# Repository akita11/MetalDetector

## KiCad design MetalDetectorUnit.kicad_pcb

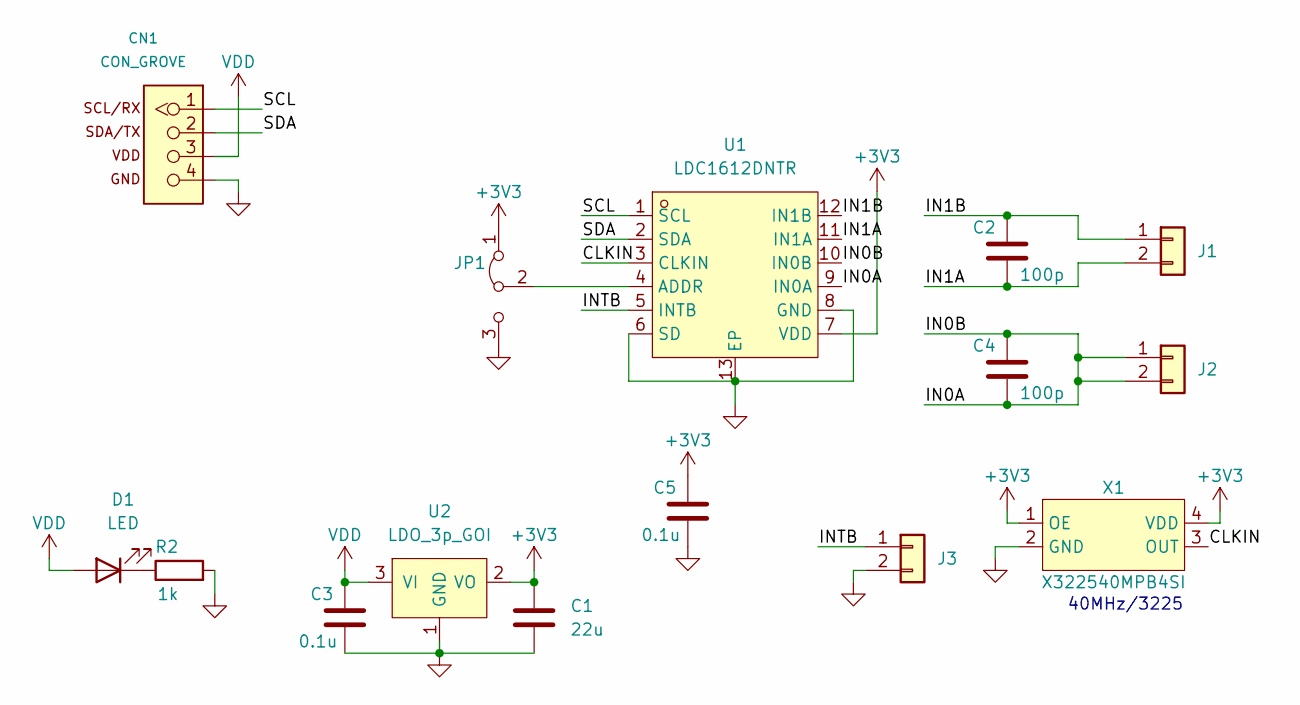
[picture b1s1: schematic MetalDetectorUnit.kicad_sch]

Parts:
C1: 22u; C_0603_1608Metric; LCSC C19702
C2, C4: 100p; C_0603_1608Metric; LCSC C14858
C3, C5: 0.1u; C_0603_1608Metric; LCSC C14663
CN1: CON_GROVE; CON_GROVE_H
D1: LED; D_0603_1608Metric
J1, J2, J3: Conn_01x02; PinHeader_1x02_P2.54mm_Vertical
JP1: Jumper_3_Bridged12; SolderJumper-3_P1.3mm_Bridged12_Pad1.0x1.5mm
R2: 1k; R_0603_1608Metric
U1: LDC1612DNTR; WSON-12_L4.0-W4.0-P0.50-BL-EP; MPN LDC1612DNTR; LCSC Part C1847959
U2: LDO_3p_GOI; SOT-23; LCSC C41376473
X1: X322540MPB4SI; OSC-SMD_4P-L3.2-W2.5-BL; LCSC Part C9010

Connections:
+3V3: C1.1, C5.1, JP1.1 (A), U1.7 (VDD), U2.2 (VO), X1.1 (OE), X1.4 (VDD)
/CLKIN: U1.3 (CLKIN), X1.3 (OUT)
/IN0A: C4.1, C4.2, J2.1, J2.2, U1.9 (IN0A), U1.10 (IN0B)
/IN1A: C2.2, J1.2, U1.11 (IN1A)
/IN1B: C2.1, J1.1, U1.12 (IN1B)
/INTB: J3.1, U1.5 (INTB)
/SCL: CN1.1, U1.1 (SCL)
/SDA: CN1.2, U1.2 (SDA)
GND: C1.2, C3.2, C5.2, CN1.4, J3.2, JP1.3 (B), R2.2, U1.6 (SD), U1.8 (GND), U1.13 (EP), U2.1 (GND), X1.2 (GND)
unnamed: D1.1 (K), R2.1
unnamed: JP1.2 (C), U1.4 (ADDR)
VDD: C3.1, CN1.3, D1.2 (A), U2.3 (VI)

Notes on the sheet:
40MHz/3225

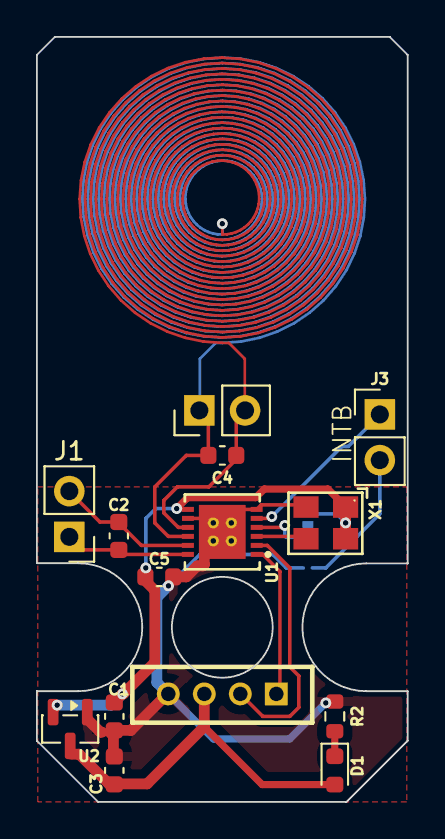
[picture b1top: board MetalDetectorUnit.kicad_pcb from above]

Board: 2 copper layers, 20.6 x 42.5 mm, 15 parts (1 on the bottom side), 12 nets.
